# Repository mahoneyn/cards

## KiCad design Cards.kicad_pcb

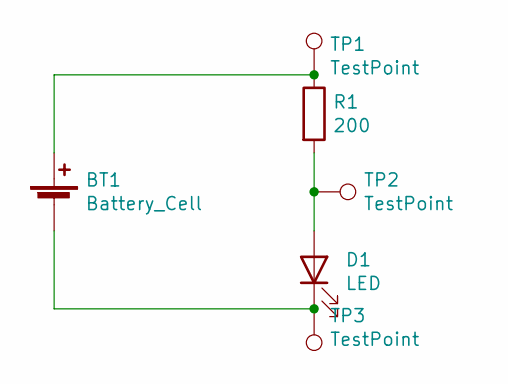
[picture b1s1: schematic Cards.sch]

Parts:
BT1: Battery_Cell; S8211-46R
D1: LED; LED_0603_HandSoldering
R1: 200; R_0603_HandSoldering
TP1, TP2, TP3: TestPoint; Measurement_Point_Round-TH_Small

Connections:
unnamed: BT1.1 (+), R1.1, TP1.1
unnamed: BT1.2 (-), D1.1 (K), TP3.1
unnamed: D1.2 (A), R1.2, TP2.1

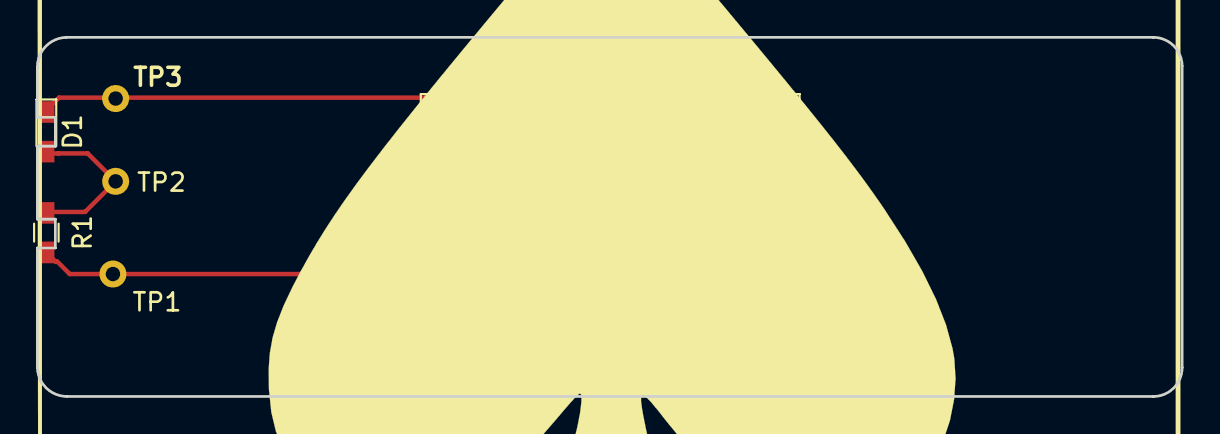
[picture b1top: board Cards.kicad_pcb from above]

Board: 2 copper layers, 63.6 x 20.0 mm, 6 parts (0 on the bottom side), 3 nets.

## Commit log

2020-10-05 Added KiCAD files
2020-10-06 Modified board edge to approx 1 in by 3 in and removed mask layers
2020-10-06 Modified board to just cover the test points and board edge
